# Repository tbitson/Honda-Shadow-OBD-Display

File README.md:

# Honda Shadow OBD Display

This is a 'in-work'n project. Many aspects may not work yet!
 
A Teensy 3.2 based OBD display for a 
2013 Honda Shadow 750 Aero. 

There are 2 parts to this project:
1) A level converter/interface board that connects to the diagnostic connector on the motorcycle. This provides power and opto-isolates the OBD signal. The OBD signal is level shifted to a 3.3V logic level. The schmatic and Eagle PCB files are included.

2) A Teensy 3.2 microcontroller connected to a 240x320 LCD Touchscreen. This displays the various options and OBD values. GThe Teensy and LCD are from PRJC.com. It uses the PCB LCD adapter from PRJC to connect the LCD to the Teensy, and is available from the OSHPark.com.

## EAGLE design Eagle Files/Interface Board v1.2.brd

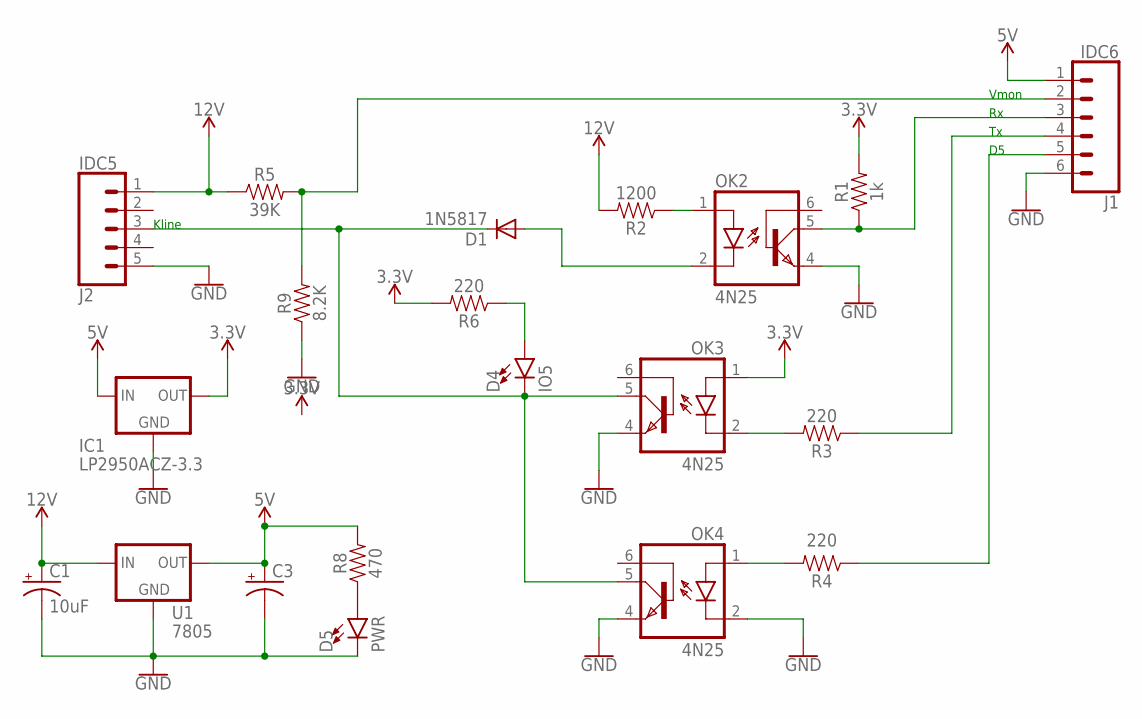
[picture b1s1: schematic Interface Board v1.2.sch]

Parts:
C1, C3: 10uF; CPOL-RADIAL-2.5MM-5MM
D1: 1N5817; DO41-10
D4: IO5; LED_5MM
D5: PWR; LED_5MM
IC1: LP2950ACZ-3.3; TO92
J1: IDC6; 1X06_LONGPADS
J2: IDC5; 1X05
OK2, OK3, OK4: 4N25; DIL06
R1: 1k; AXIAL-0.3
R2: 1200; AXIAL-0.3
R3, R4, R6: 220; AXIAL-0.3
R5: 39K; AXIAL-0.3
R8: 470; AXIAL-0.3
R9: 8.2K; AXIAL-0.3
U1: 7805; TO-220-ALT

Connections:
3.3V: IC1.1 (OUT), OK3.1 (A), R1.P$2 (2), R6.P$2 (2)
5V: C3.1 (+), IC1.3 (IN), J1.1, R8.P$2 (2), U1.OUT
12V: C1.1 (+), J2.1, R2.P$2 (2), R5.P$1 (1), U1.IN
GND: C1.2 (-), C3.2 (-), D5.K (C), IC1.2 (GND), J1.6, J2.5, OK2.4 (EMI), OK3.4 (EMI), OK4.2 (C), OK4.4 (EMI), R9.P$1 (1), U1.GND
KLINE: D1.C, D4.K (C), J2.3, OK3.5 (COL), OK4.5 (COL)
unnamed: OK3.2 (C), R3.P$2 (2)
unnamed: J1.4, R3.P$1 (1)
unnamed: D1.A, OK2.2 (C)
unnamed: D4.A, R6.P$1 (1)
unnamed: J1.3, OK2.5 (COL), R1.P$1 (1)
unnamed: OK2.1 (A), R2.P$1 (1)
unnamed: D5.A, R8.P$1 (1)
unnamed: J1.5, R4.P$1 (1)
unnamed: OK4.1 (A), R4.P$2 (2)
VMON: J1.2, R5.P$2 (2), R9.P$2 (2)

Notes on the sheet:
Vmon
Kline

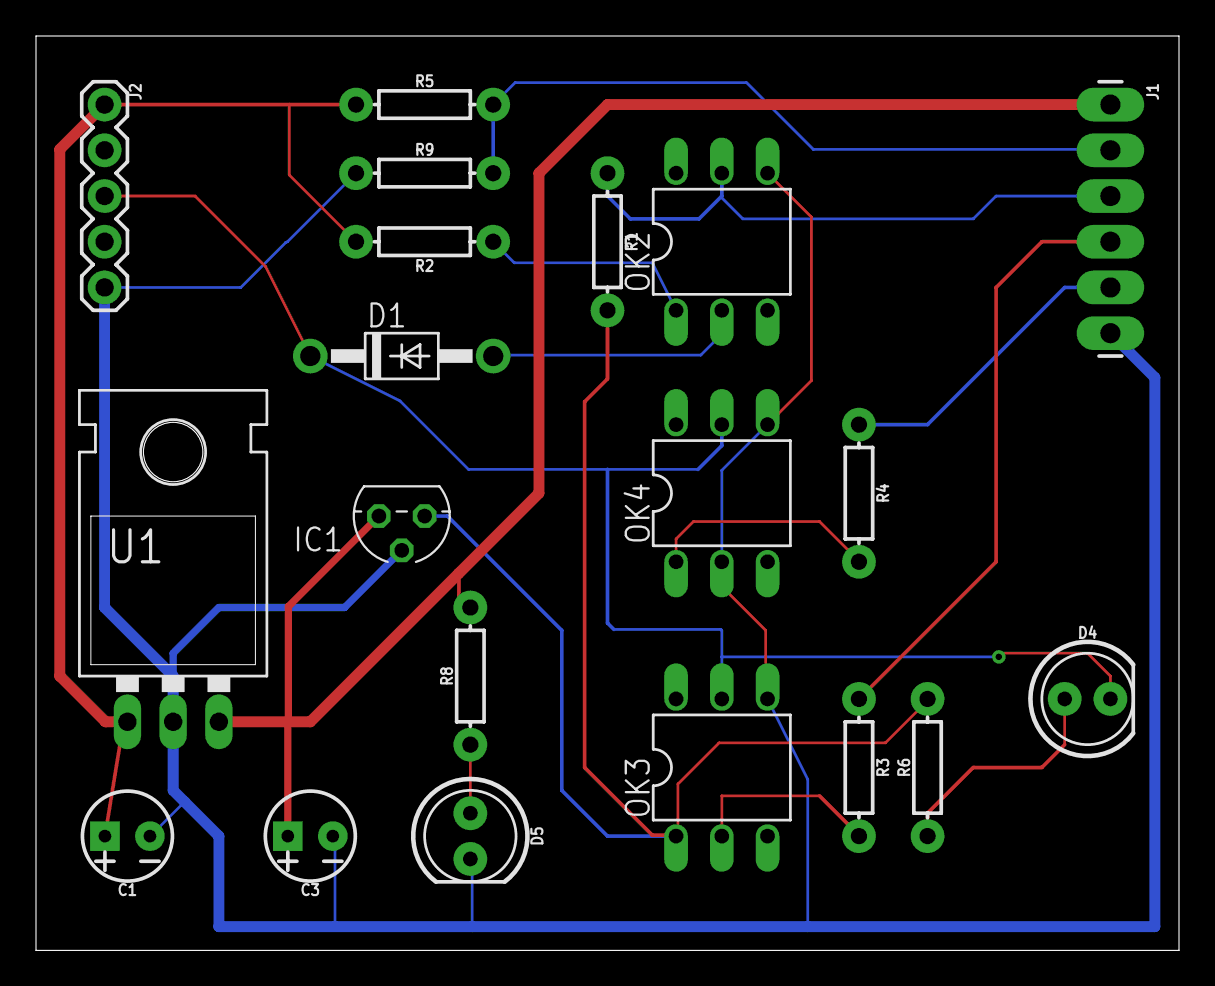
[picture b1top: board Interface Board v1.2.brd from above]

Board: 2 copper layers, 63.5 x 50.8 mm, 20 parts (0 on the bottom side), 15 nets.

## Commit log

2020-10-01 Initial Release
    An OBD interface and display for a 2013 Honda Shadow Aero.

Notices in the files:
parts and their libraries:
SparkFun-Capacitors: Licensing: Creative Commons ShareAlike 4.0 International - https://creativecommons.org/licenses/by-sa/4.0
